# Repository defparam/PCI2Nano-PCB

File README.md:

# PCI2Nano Reference Platform

Welcome to the PCI2Nano Reference Platform repo. In this repo you'll find an inexpensive suggested Reference Platform for designing and testing PCI functions on a DE0-Nano FPGA to an x86 host. I have personally built/connected/tested every single one of these components and can confirm they work for fast iterative PCI development.

The design collateral that is included with this repo are the kicad design files for the PCI2Nano breakout board and a Quartus project that contains all the correct PCI pinout constraints for the PCI2Nano breakout board. This repo does not contain an actual PCI core written in verilog. For an example PCI core implementation with a UART check out the PCI2Nano-RTL repo here: https://github.com/defparam/PCI2Nano-RTL/

<br />This work is licensed under a <a rel="license" href="http://creativecommons.org/licenses/by-sa/4.0/">Creative Commons Attribution-ShareAlike 4.0 International License</a>.

# Demo
My l337-Communication Controller

# Reference Platform Parts List
| Part |  Description| Price | 
|--|--|--|
| DE0-Nano |  FPGA Board|~$100.00
| Seeed Odyssey X86J4105 SBC | SIngle Board Computer | ~$185.00
|PCI2Nano Breakout PCB|Coverts PCI to DE0-Nano GPIO | ~$45 (OSHPark for 3)
|Startech PEX1PCI1| Converts PCIe to PCI | ~$40
|M.2 Key M Extender PCIE x16 | Break out M.2 to PCIe x16 | ~$32
2x 100mil 40-pin IDC sockets| Soldered to the PCB| ~$1-$2

# Directions
1) Mount the Extender cable into the Odyssey M.2 M Key slot. If you have standoffs you can affix the x16 connector of the extender to the SBC as shown in the picture above.
2) Mount the PEX1PCI1 onto the x16 connector. Supplying the molex power I believe is not required since it is used to power the 5V rails of a mounted PCI device, the PCI2Nano doesn't use this 5V rail (unless you bridge it to the Nano's 5V GPIO power pin via the board shunt). However it is best to power the nano through its USB cable
3) Connect the PCI2Nano breakout board to the DE0-Nano, make sure that the USB of the nano points in the correct direction as specified by the silkscreen
4) Connect the PCI side of the PCI2Nano onto the PEX1PCI1, make sure it is connected in the orientation as indicated by the silk screen. The arrow indicating the chassis side should be pointed to the externel side of the PEX1PCI1

# PCB board
There is a small amount of soldering involved with the PCB board to connect the 100mil IDC socket to the PCB board.

# Parts
The DE0-Nano:

The PCI2Nano PCB:

The PEX1PCI1 PCIe-2-PCI Bridge:

The Seeed Odyssey X86J4105 SBC:

The M.2 Key M Extender PCIE x16:

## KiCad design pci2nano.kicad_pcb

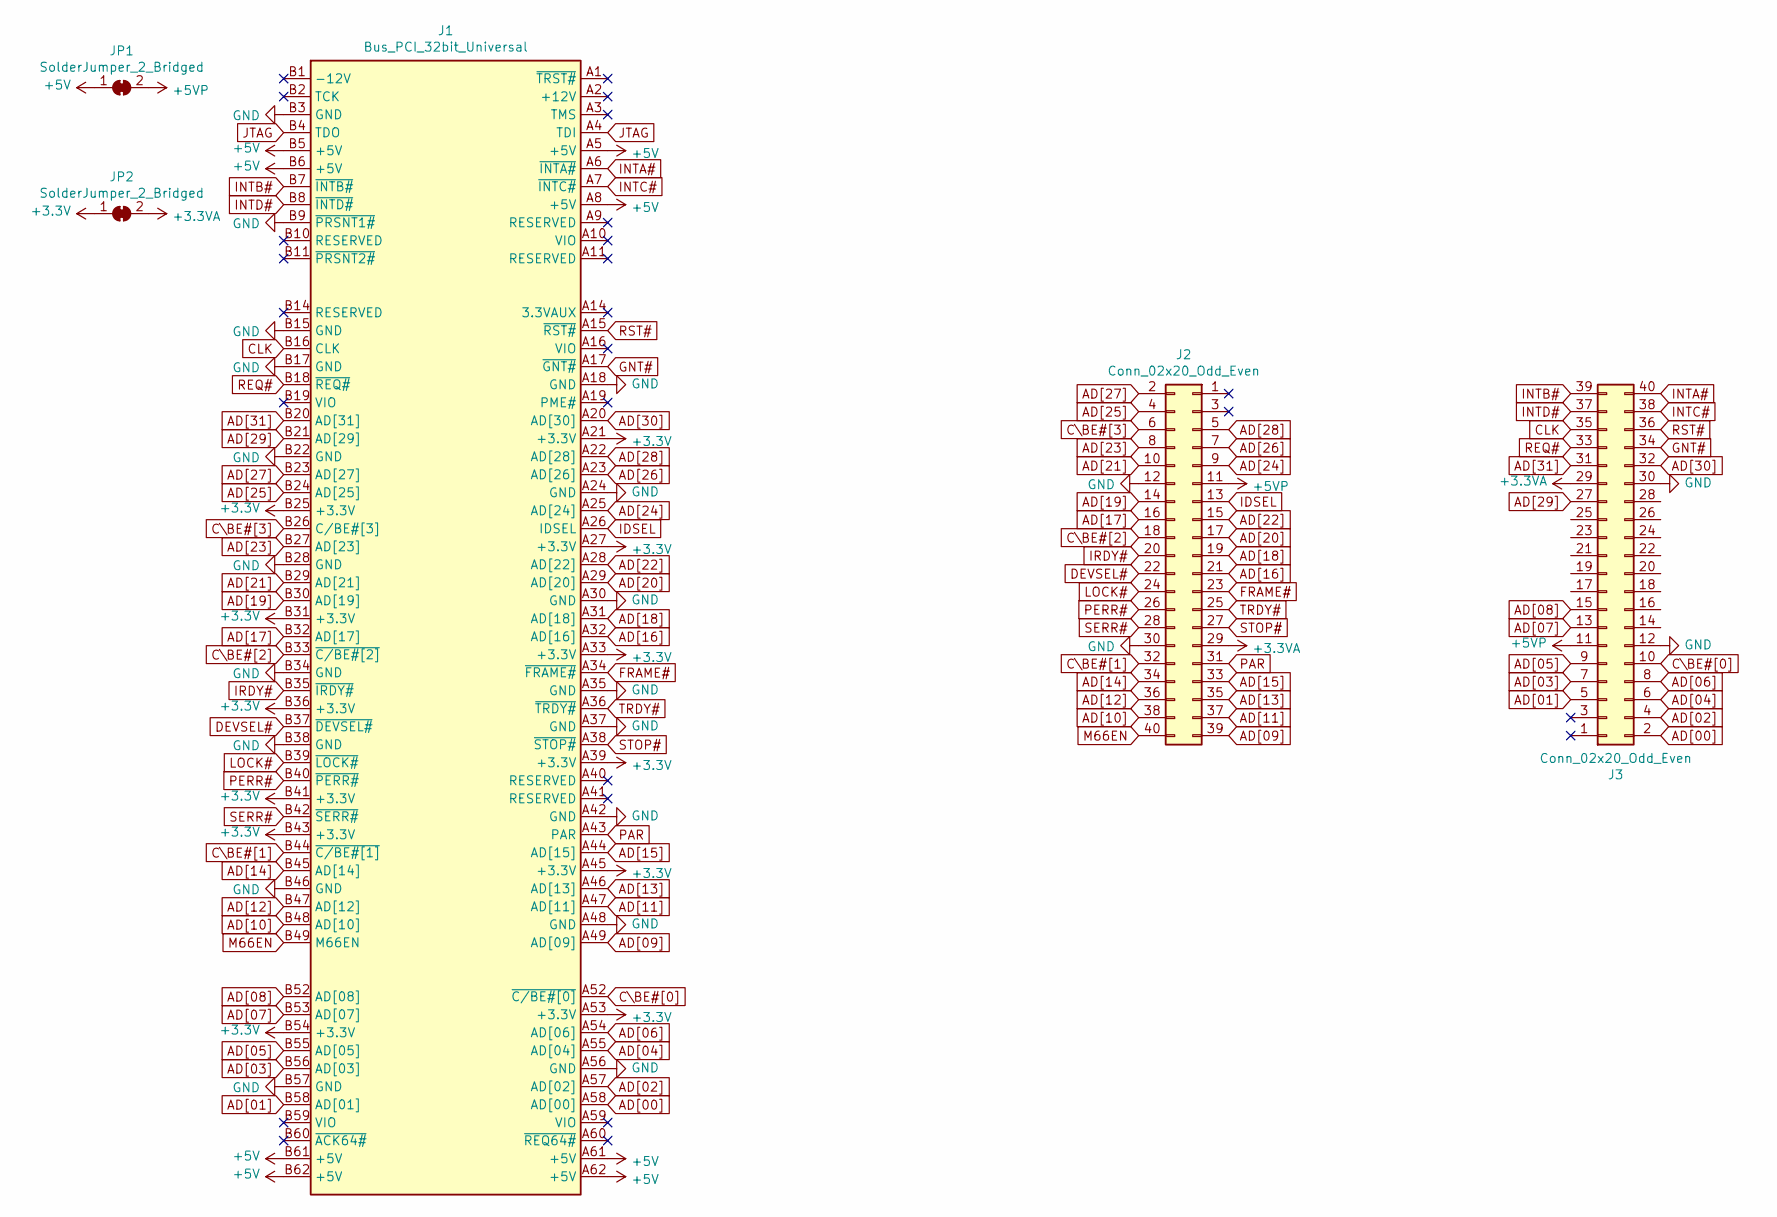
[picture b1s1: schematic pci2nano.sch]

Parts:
J1: Bus_PCI_32bit_Universal; BUS_PCI_UNIVERSAL
J2, J3: Conn_02x20_Odd_Even; PinHeader_2x20_P2.54mm_Vertical
JP1, JP2: SolderJumper_2_Bridged; SolderJumper-2_P1.3mm_Open_Pad1.0x1.5mm

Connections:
+3.3VA: J2.29, J3.29, JP2.2 (B)
+3V3: J1.A21 (+3.3V), J1.A27 (+3.3V), J1.A33 (+3.3V), J1.A39 (+3.3V), J1.A45 (+3.3V), J1.A53 (+3.3V), J1.B25 (+3.3V), J1.B31 (+3.3V), J1.B36 (+3.3V), J1.B41 (+3.3V), J1.B43 (+3.3V), J1.B54 (+3.3V), JP2.1 (A)
+5V: J1.A5 (+5V), J1.A8 (+5V), J1.A61 (+5V), J1.A62 (+5V), J1.B5 (+5V), J1.B6 (+5V), J1.B61 (+5V), J1.B62 (+5V), JP1.1 (A)
+5VP: J2.11, J3.11, JP1.2 (B)
AD[00]: J1.A58 (AD[00]), J3.2
AD[01]: J1.B58 (AD[01]), J3.5
AD[02]: J1.A57 (AD[02]), J3.4
AD[03]: J1.B56 (AD[03]), J3.7
AD[04]: J1.A55 (AD[04]), J3.6
AD[05]: J1.B55 (AD[05]), J3.9
AD[06]: J1.A54 (AD[06]), J3.8
AD[07]: J1.B53 (AD[07]), J3.13
AD[08]: J1.B52 (AD[08]), J3.15
AD[09]: J1.A49 (AD[09]), J2.39
AD[10]: J1.B48 (AD[10]), J2.38
AD[11]: J1.A47 (AD[11]), J2.37
AD[12]: J1.B47 (AD[12]), J2.36
AD[13]: J1.A46 (AD[13]), J2.35
AD[14]: J1.B45 (AD[14]), J2.34
AD[15]: J1.A44 (AD[15]), J2.33
AD[16]: J1.A32 (AD[16]), J2.21
AD[17]: J1.B32 (AD[17]), J2.16
AD[18]: J1.A31 (AD[18]), J2.19
AD[19]: J1.B30 (AD[19]), J2.14
AD[20]: J1.A29 (AD[20]), J2.17
AD[21]: J1.B29 (AD[21]), J2.10
AD[22]: J1.A28 (AD[22]), J2.15
AD[23]: J1.B27 (AD[23]), J2.8
AD[24]: J1.A25 (AD[24]), J2.9
AD[25]: J1.B24 (AD[25]), J2.4
AD[26]: J1.A23 (AD[26]), J2.7
AD[27]: J1.B23 (AD[27]), J2.2
AD[28]: J1.A22 (AD[28]), J2.5
AD[29]: J1.B21 (AD[29]), J3.27
AD[30]: J1.A20 (AD[30]), J3.32
AD[31]: J1.B20 (AD[31]), J3.31
CLK: J1.B16 (CLK), J3.35
C\BE#[0]: J1.A52 (~C/BE#[0]), J3.10
C\BE#[1]: J1.B44 (~C/BE#[1]), J2.32
C\BE#[2]: J1.B33 (~C/BE#[2]), J2.18
C\BE#[3]: J1.B26 (C/BE#[3]), J2.6
DEVSEL#: J1.B37 (~DEVSEL#), J2.22
FRAME#: J1.A34 (~FRAME#), J2.23
GND: J1.A18 (GND), J1.A24 (GND), J1.A30 (GND), J1.A35 (GND), J1.A37 (GND), J1.A42 (GND), J1.A48 (GND), J1.A56 (GND), J1.B3 (GND), J1.B9 (~PRSNT1#), J1.B15 (GND), J1.B17 (GND), J1.B22 (GND), J1.B28 (GND), J1.B34 (GND), J1.B38 (GND), J1.B46 (GND), J1.B57 (GND), J2.12, J2.30, J3.12, J3.30
GNT#: J1.A17 (~GNT#), J3.34
IDSEL: J1.A26 (IDSEL), J2.13
INTA#: J1.A6 (~INTA#), J3.40
INTB#: J1.B7 (~INTB#), J3.39
INTC#: J1.A7 (~INTC#), J3.38
INTD#: J1.B8 (~INTD#), J3.37
IRDY#: J1.B35 (~IRDY#), J2.20
JTAG: J1.A4 (TDI), J1.B4 (TDO)
LOCK#: J1.B39 (~LOCK#), J2.24
M66EN: J1.B49 (M66EN), J2.40
PAR: J1.A43 (PAR), J2.31
PERR#: J1.B40 (~PERR#), J2.26
REQ#: J1.B18 (~REQ#), J3.33
RST#: J1.A15 (~RST#), J3.36
SERR#: J1.B42 (~SERR#), J2.28
STOP#: J1.A38 (~STOP#), J2.27
TRDY#: J1.A36 (~TRDY#), J2.25

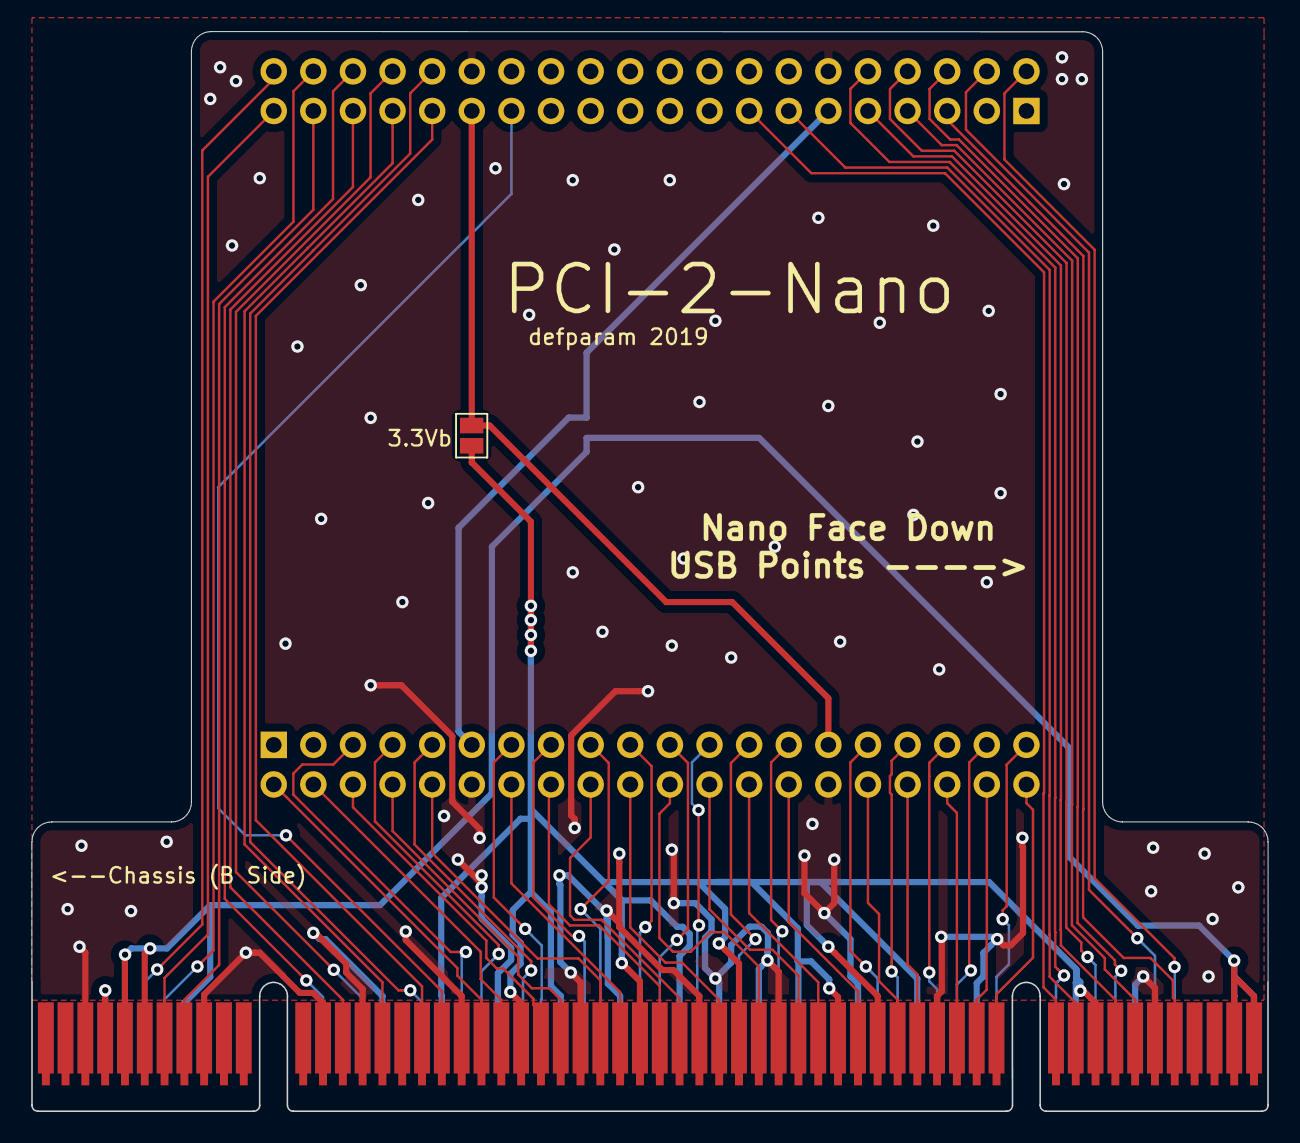
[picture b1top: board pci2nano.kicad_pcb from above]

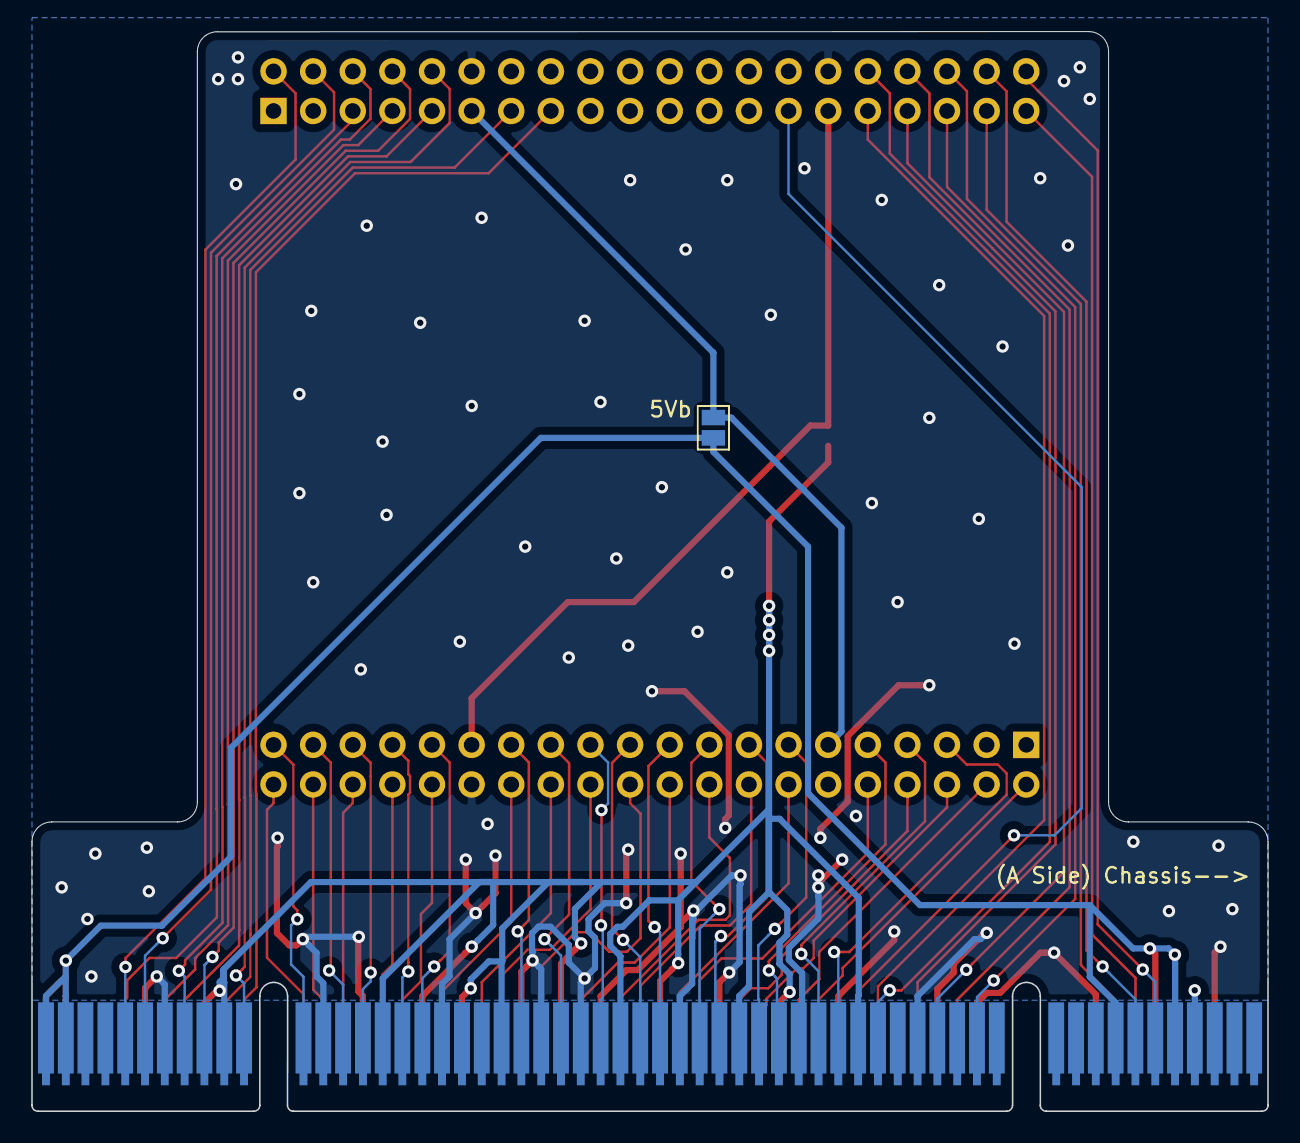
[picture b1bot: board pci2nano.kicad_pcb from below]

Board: 2 copper layers, 79.2 x 69.2 mm, 5 parts (3 on the bottom side), 61 nets.

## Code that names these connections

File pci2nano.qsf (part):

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set_location_assignment PIN_R12 -to AD[24]
set_location_assignment PIN_T11 -to AD[21]

set_location_assignment PIN_T10 -to IDSEL
set_location_assignment PIN_R11 -to AD[19]
set_location_assignment PIN_P11 -to AD[22]
set_location_assignment PIN_R10 -to AD[17]
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set_location_assignment PIN_R14 -to STOPn
set_location_assignment PIN_N16 -to SERRn

set_location_assignment PIN_N15 -to PAR
set_location_assignment PIN_P14 -to CBEn[1]
set_location_assignment PIN_L14 -to AD[15]
set_location_assignment PIN_N14 -to AD[14]
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set_location_assignment PIN_J16 -to AD[11]
set_location_assignment PIN_K15 -to AD[10]
set_location_assignment PIN_J13 -to AD[09]
set_location_assignment PIN_J14 -to M66EN

set_global_assignment -name MIN_CORE_JUNCTION_TEMP 0
set_global_assignment -name MAX_CORE_JUNCTION_TEMP 85
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
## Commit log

2020-12-08 Create LICENSE
